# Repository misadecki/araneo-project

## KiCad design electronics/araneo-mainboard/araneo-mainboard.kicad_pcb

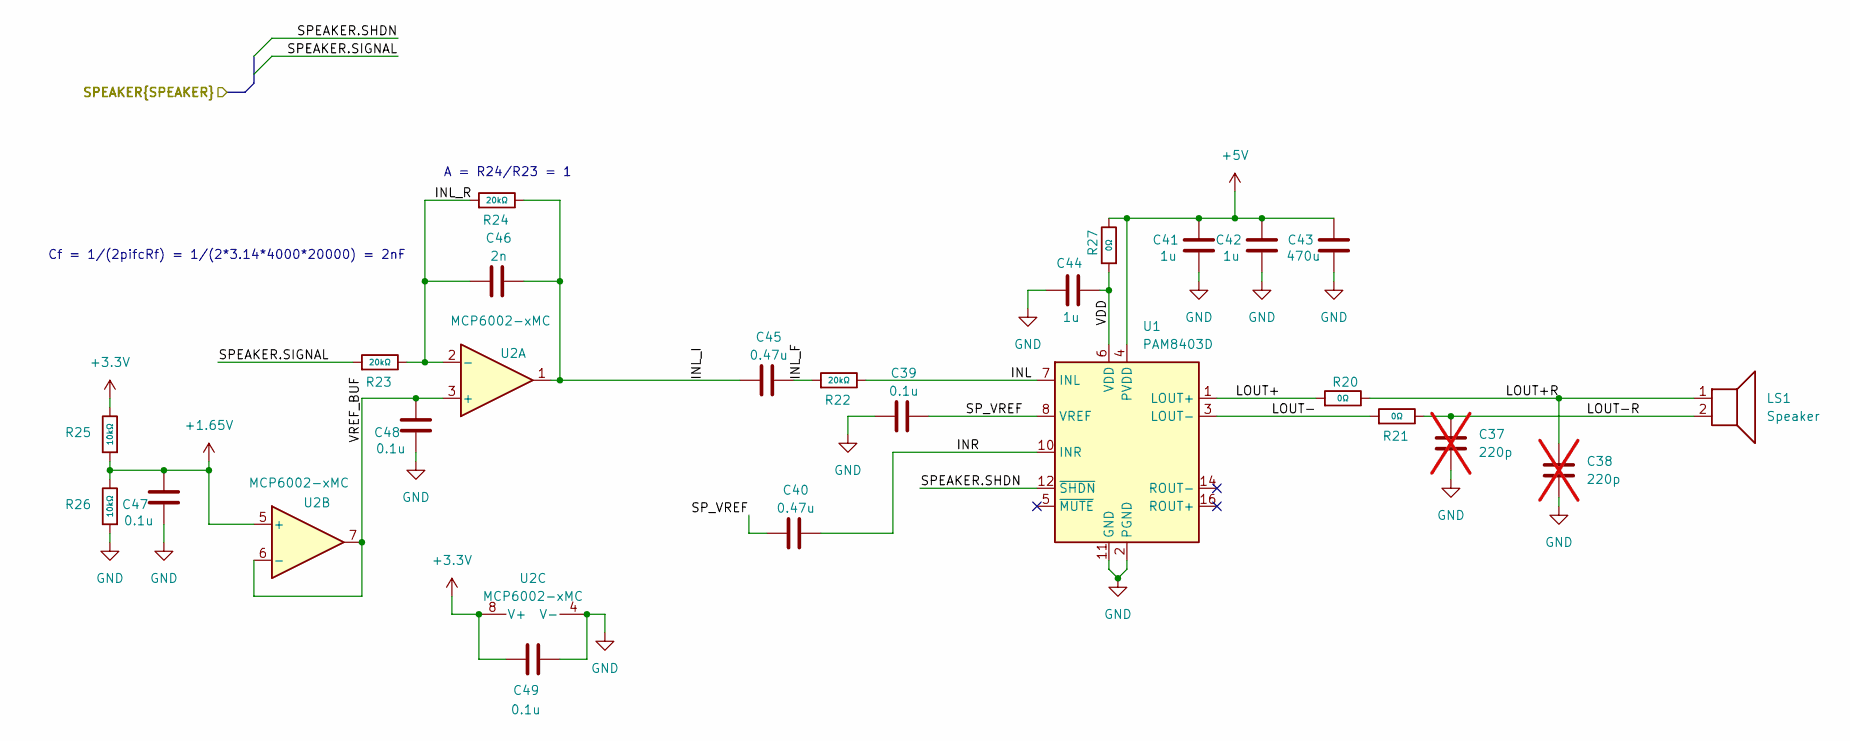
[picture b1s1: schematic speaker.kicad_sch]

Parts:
C37, C38: 220p; C_0603; not fitted
C39, C47, C48, C49: 0.1u; C_0402
C40, C45: 0.47u; C_0402
C41, C42, C44: 1u; C_0402
C43: 470u; CP_Radial_D10.0mm_P5.00mm
C46: 2n; C_0603
LS1: Speaker; ScrewTerminal_1x02_P3.5mm_Blue
R20, R21, R27: 0Ω; R_0603; Overload Voltage (Max) 50V; Tolerance ±1%; Part 0402WGF1201TCE; LCSC C25862
R22, R23, R24: 20kΩ; R_0603; Overload Voltage (Max) 50V; Tolerance ±1%; Part 0402WGF1201TCE; LCSC C25862
R25, R26: 10kΩ; R_0402; Overload Voltage (Max) 50V; Tolerance ±1%; Part 0402WGF1201TCE; LCSC C25862
U1: PAM8403D; SOIC-16_3.9x9.9mm_P1.27mm
U2: MCP6002-xMC; SOIC-8_L4.9-W3.9-P1.27-LS6.0-BL

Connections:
+1.65V: C47.2, R25.1, R26.2, U2.5 (+)
+3.3V: C49.2, R25.2, U2.8 (V+); also elsewhere on the board
+5V: C41.2, C42.2, C43.2, R27.2, U1.4 (PVDD), U1.13 (PVDD); also elsewhere on the board
/MCU/SPEAKER.SHDN: U1.12 (~SHDN); also elsewhere on the board
/MCU/SPEAKER.SIGNAL: R23.1; also elsewhere on the board
/Speaker/INL: R22.2, U1.7 (INL)
/Speaker/INL_F: C45.2, R22.1
/Speaker/INL_I: C45.1, C46.2, R24.2, U2.1
/Speaker/INL_R: C46.1, R23.2, R24.1, U2.2 (-)
/Speaker/INR: C40.2, U1.10 (INR)
/Speaker/LOUT+: R20.1, U1.1 (LOUT+)
/Speaker/LOUT+R: C38.1, LS1.1, R20.2
/Speaker/LOUT-: R21.1, U1.3 (LOUT-)
/Speaker/LOUT-R: C37.1, LS1.2, R21.2
/Speaker/SP_VREF: C39.2, C40.1, U1.8 (VREF)
/Speaker/VDD: C44.1, R27.1, U1.6 (VDD)
/Speaker/VREF_BUF: C48.2, U2.3 (+), U2.6 (-), U2.7
GND: C37.2, C38.2, C39.1, C41.1, C42.1, C43.1, C44.2, C47.1, C48.1, C49.1, R26.1, U1.2 (PGND), U1.11 (GND), U1.15 (PGND), U2.4 (V-); also elsewhere on the board

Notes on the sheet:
Cf = 1/(2pifcRf) = 1/(2*3.14*4000*20000) = 2nF
A = R24/R23 = 1

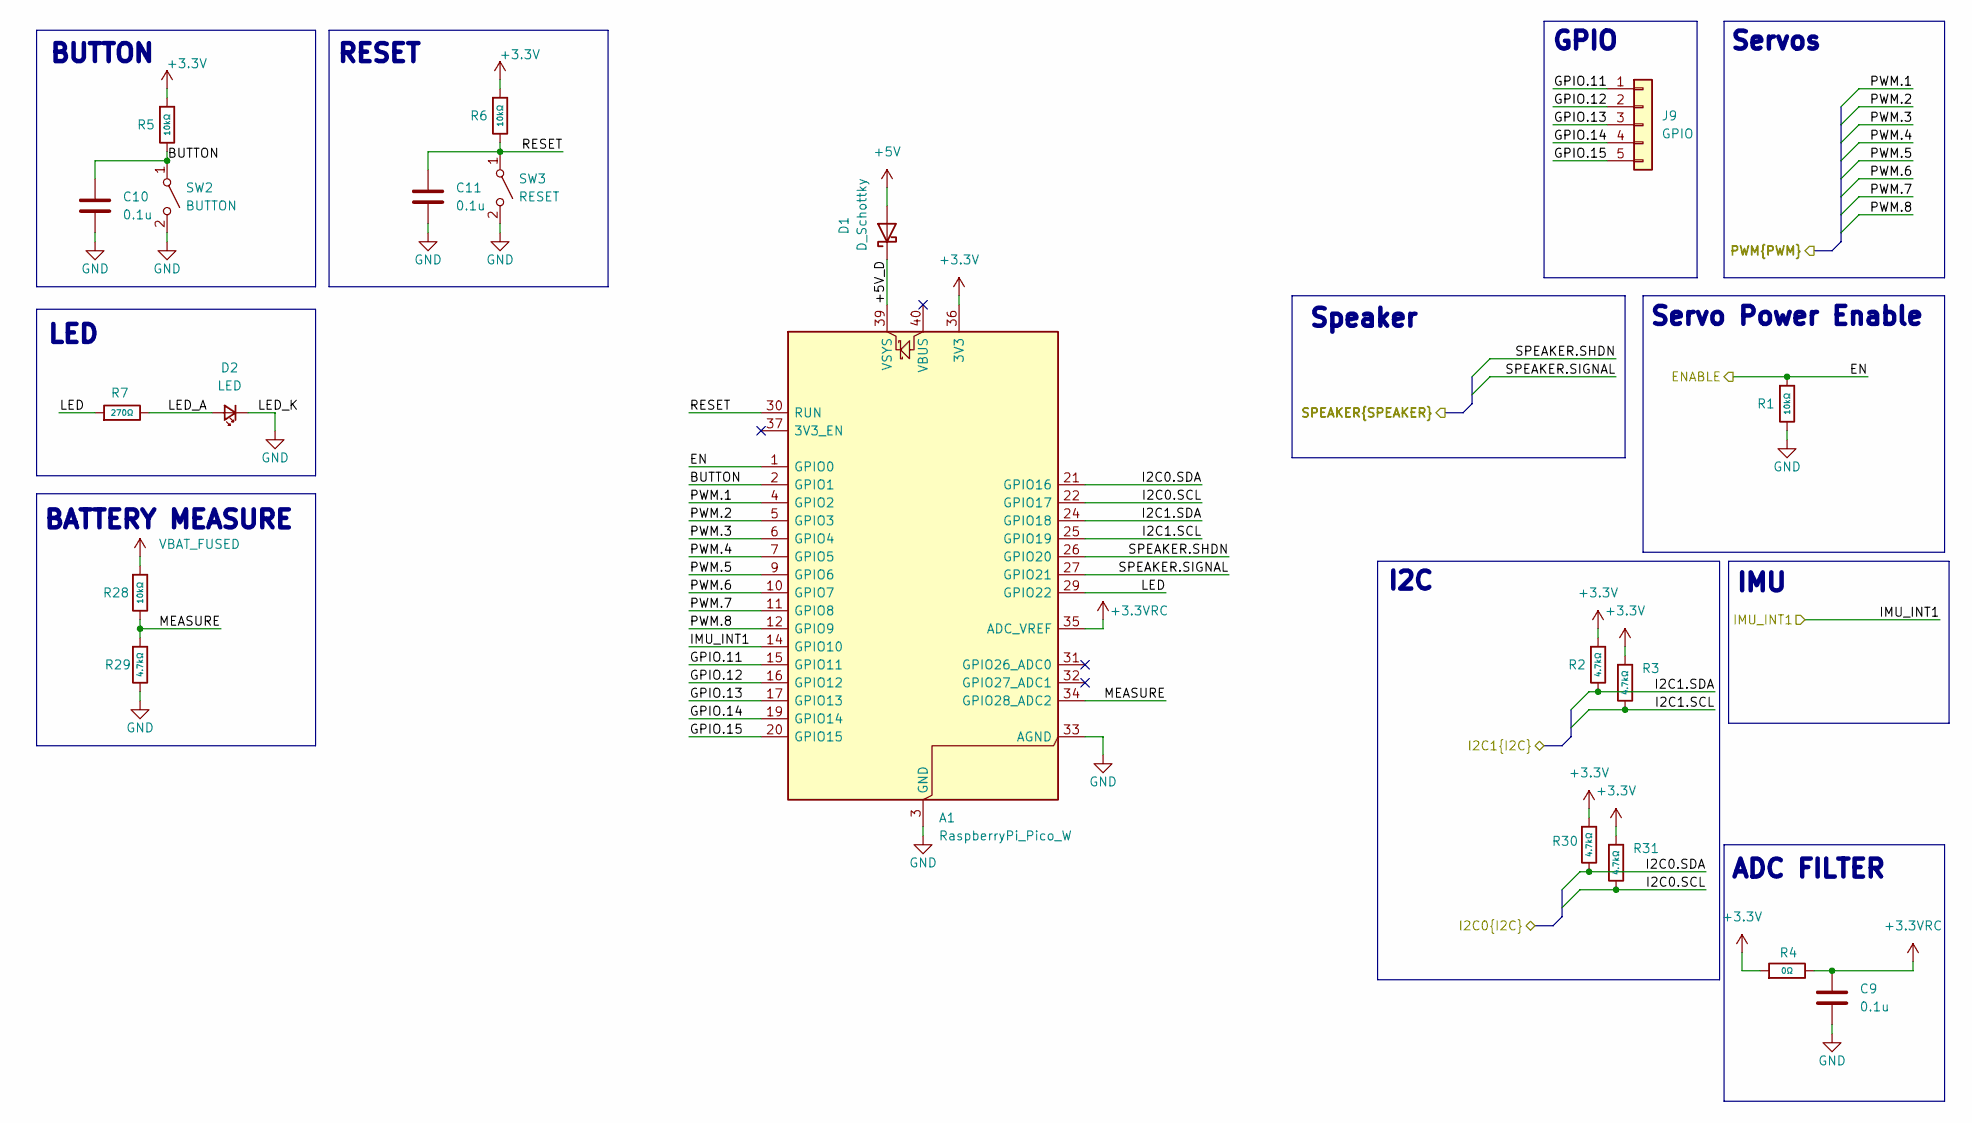
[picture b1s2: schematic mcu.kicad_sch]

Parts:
A1: RaspberryPi_Pico_W; RaspberryPi_Pico_Common_THT
C9: 0.1u; C_0603
C10, C11: 0.1u; C_0402
D1: D_Schottky; SOD-123
D2: LED; D_0603
J9: GPIO; PinHeader_1x05_P2.54mm_Vertical
R1, R5, R6, R28: 10kΩ; R_0402; Overload Voltage (Max) 50V; Tolerance ±1%; Part 0402WGF1201TCE; LCSC C25862
R2, R3, R29, R30, R31: 4.7kΩ; R_0402; Overload Voltage (Max) 50V; Tolerance ±1%; Part 0402WGF1201TCE; LCSC C25862
R4: 0Ω; R_0603; Overload Voltage (Max) 50V; Tolerance ±1%; Part 0402WGF1201TCE; LCSC C25862
R7: 270Ω; R_0603; Overload Voltage (Max) 50V; Tolerance ±1%; Part 0402WGF1201TCE; LCSC C25862
SW2: BUTTON; ScrewTerminal_1x02_P3.5mm_Blue
SW3: RESET; SW_SPST_TL3305B

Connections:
+3.3V: A1.36 (3V3), R2.1, R3.1, R4.1, R5.1, R6.1, R30.1, R31.1; also elsewhere on the board
+3.3VRC: A1.35 (ADC_VREF), C9.1, R4.2
+5V: D1.2 (A); also elsewhere on the board
/IMU/I2C1.SCL: A1.25 (GPIO19), R3.2; also elsewhere on the board
/IMU/I2C1.SDA: A1.24 (GPIO18), R2.2; also elsewhere on the board
/MCU/+5V_D: A1.39 (VSYS), D1.1 (K)
/MCU/BUTTON: A1.2 (GPIO1), C10.1, R5.2, SW2.1 (A)
/MCU/EN: A1.1 (GPIO0), R1.1; also elsewhere on the board
/MCU/GPIO.11: A1.15 (GPIO11), J9.1
/MCU/GPIO.12: A1.16 (GPIO12), J9.2
/MCU/GPIO.13: A1.17 (GPIO13), J9.3
/MCU/GPIO.14: A1.19 (GPIO14), J9.4
/MCU/GPIO.15: A1.20 (GPIO15), J9.5
/MCU/I2C0.SCL: A1.22 (GPIO17), R31.2; also elsewhere on the board
/MCU/I2C0.SDA: A1.21 (GPIO16), R30.2; also elsewhere on the board
/MCU/IMU_INT1: A1.14 (GPIO10); also elsewhere on the board
/MCU/LED: A1.29 (GPIO22), R7.1
/MCU/LED_A: D2.2 (A), R7.2
/MCU/MEASURE: A1.34 (GPIO28_ADC2), R28.2, R29.1
/MCU/PWM.1: A1.4 (GPIO2); also elsewhere on the board
/MCU/PWM.2: A1.5 (GPIO3); also elsewhere on the board
/MCU/PWM.3: A1.6 (GPIO4); also elsewhere on the board
/MCU/PWM.4: A1.7 (GPIO5); also elsewhere on the board
/MCU/PWM.5: A1.9 (GPIO6); also elsewhere on the board
/MCU/PWM.6: A1.10 (GPIO7); also elsewhere on the board
/MCU/PWM.7: A1.11 (GPIO8); also elsewhere on the board
/MCU/PWM.8: A1.12 (GPIO9); also elsewhere on the board
/MCU/RESET: A1.30 (RUN), C11.1, R6.2, SW3.1 (A)
/MCU/SPEAKER.SHDN: A1.26 (GPIO20); also elsewhere on the board
/MCU/SPEAKER.SIGNAL: A1.27 (GPIO21); also elsewhere on the board
GND: A1.3 (GND), A1.8 (GND), A1.13 (GND), A1.18 (GND), A1.23 (GND), A1.28 (GND), A1.33 (AGND), A1.38 (GND), C9.2, C10.2, C11.2, D2.1 (K), R1.2, R29.2, SW2.2 (B), SW3.2 (B); also elsewhere on the board
VBAT_FUSED: R28.1; also elsewhere on the board

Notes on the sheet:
I2C
RESET
BATTERY MEASURE
IMU
GPIO
LED
Servo Power Enable
Servos
BUTTON
Speaker
ADC FILTER

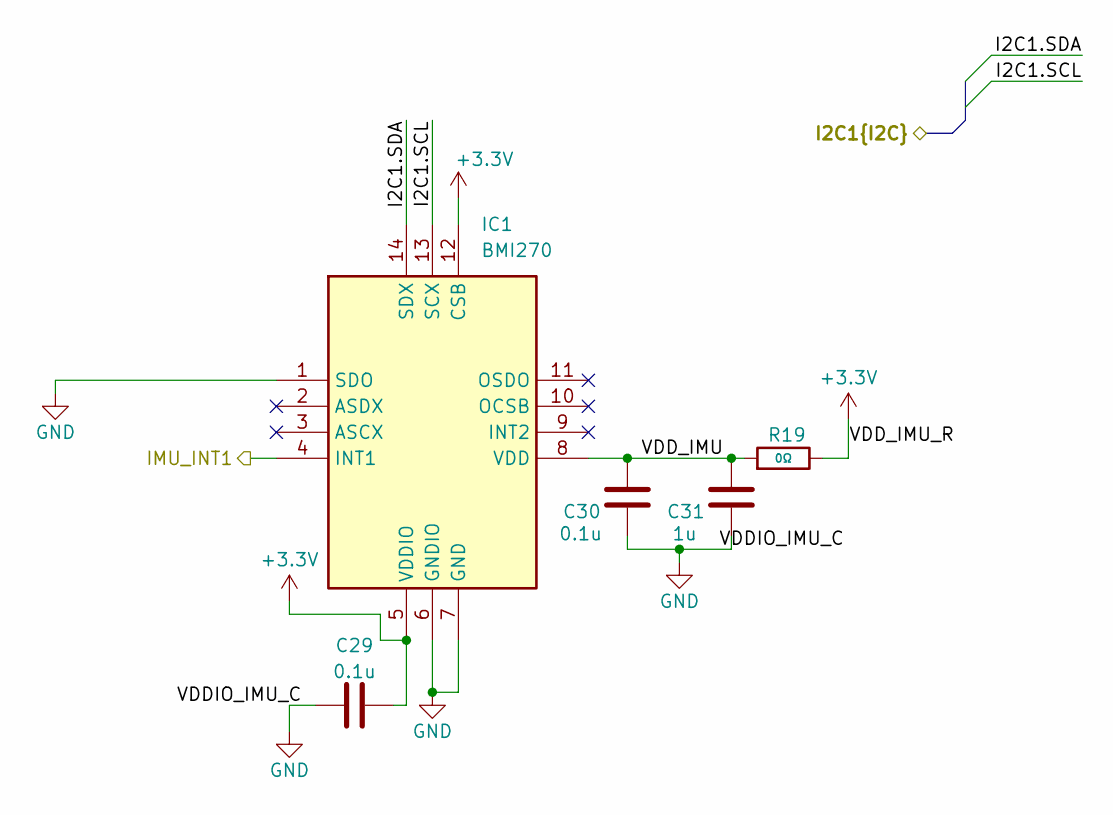
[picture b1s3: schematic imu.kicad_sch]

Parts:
C29, C30: 0.1u; C_0402
C31: 1u; C_0402
IC1: BMI270; Mouser Part Number 262-BMI270
R19: 0Ω; R_0603; Overload Voltage (Max) 50V; Tolerance ±1%; Part 0402WGF1201TCE; LCSC C25862

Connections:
+3.3V: C29.2, IC1.5 (VDDIO), IC1.12 (CSB), R19.2; also elsewhere on the board
/IMU/I2C1.SCL: IC1.13 (SCX); also elsewhere on the board
/IMU/I2C1.SDA: IC1.14 (SDX); also elsewhere on the board
/IMU/VDD_IMU: C30.2, C31.2, IC1.8 (VDD), R19.1
/MCU/IMU_INT1: IC1.4 (INT1); also elsewhere on the board
GND: C29.1, C30.1, C31.1, IC1.1 (SDO), IC1.6 (GNDIO), IC1.7 (GND); also elsewhere on the board

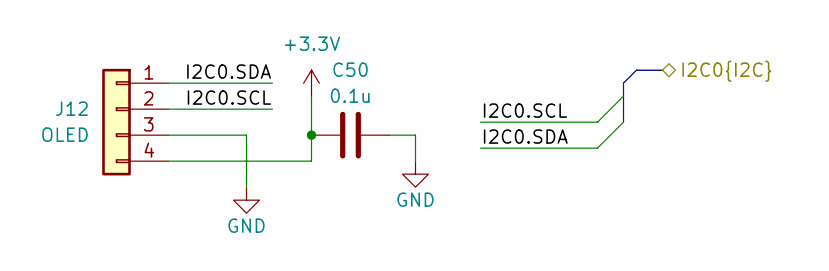
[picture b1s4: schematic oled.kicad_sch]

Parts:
C50: 0.1u; C_0402
J12: OLED; JST_XH_B4B-XH-A_1x04_P2.50mm_Vertical

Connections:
+3.3V: C50.1, J12.4; also elsewhere on the board
/MCU/I2C0.SCL: J12.2; also elsewhere on the board
/MCU/I2C0.SDA: J12.1; also elsewhere on the board
GND: C50.2, J12.3; also elsewhere on the board

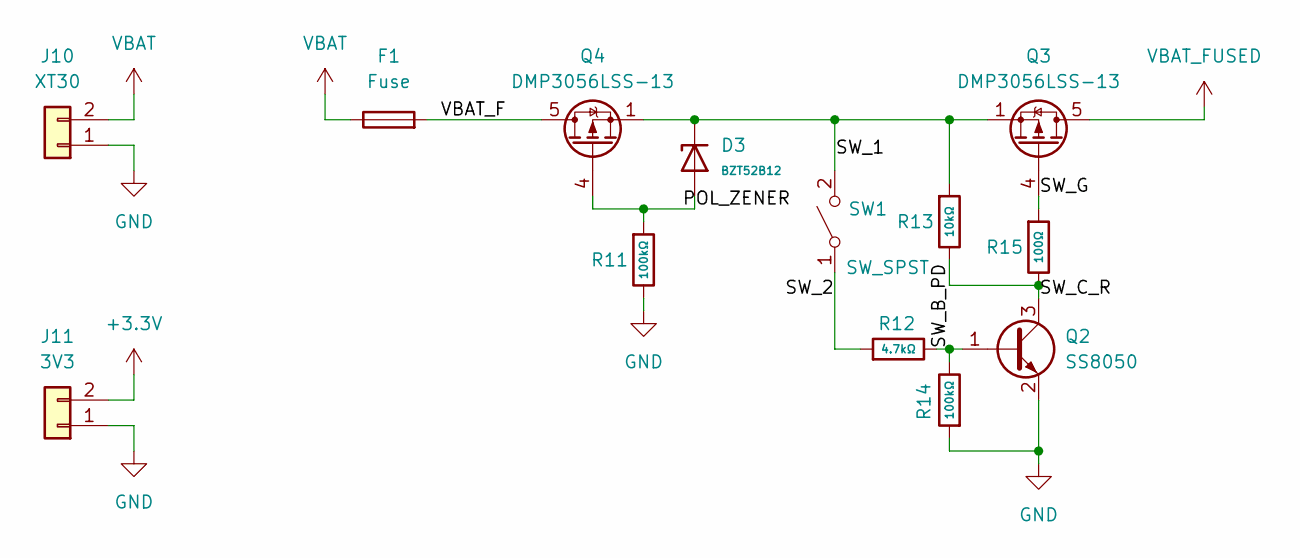
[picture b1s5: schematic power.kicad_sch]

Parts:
D3: BZT52B12; D_SOD-123; Zener Voltage (Range) 11.76V~12.24V; Zener Voltage (Nom) 12V; Part BZT52B12; LCSC C22395569
F1: Fuse; 3568
J10: XT30; AMASS_XT30U-F_1x02_P5.0mm_Vertical
J11: 3V3; PinHeader_1x02_P2.54mm_Vertical
Q2: SS8050; SOT-23
Q3, Q4: DMP3056LSS-13; SO-8
R11, R14: 100kΩ; R_0402; Overload Voltage (Max) 50V; Tolerance ±1%; Part 0402WGF1201TCE; LCSC C25862
R12: 4.7kΩ; R_0402; Overload Voltage (Max) 50V; Tolerance ±1%; Part 0402WGF1201TCE; LCSC C25862
R13: 10kΩ; R_0402; Overload Voltage (Max) 50V; Tolerance ±1%; Part 0402WGF1201TCE; LCSC C25862
R15: 100Ω; R_0402; Overload Voltage (Max) 50V; Tolerance ±1%; Part 0402WGF1201TCE; LCSC C25862
SW1: SW_SPST; ScrewTerminal_1x02_P3.5mm_Blue

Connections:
+3.3V: J11.2; also elsewhere on the board
/Power/POL_ZENER: D3.2, Q4.4 (G), R11.1
/Power/SW_1: D3.1, Q3.1 (S), Q3.2 (S), Q3.3 (S), Q4.1 (S), Q4.2 (S), Q4.3 (S), R13.1, SW1.2 (B)
/Power/SW_2: R12.1, SW1.1 (A)
/Power/SW_B_PD: Q2.1 (B), R12.2, R14.2
/Power/SW_C_R: Q2.3 (C), R13.2, R15.2
/Power/SW_G: Q3.4 (G), R15.1
/Power/VBAT_F: F1.2, Q4.5 (D), Q4.6 (D), Q4.7 (D), Q4.8 (D)
GND: J10.1, J11.1, Q2.2 (E), R11.2, R14.1; also elsewhere on the board
VBAT: F1.1, J10.2
VBAT_FUSED: Q3.5 (D), Q3.6 (D), Q3.7 (D), Q3.8 (D); also elsewhere on the board

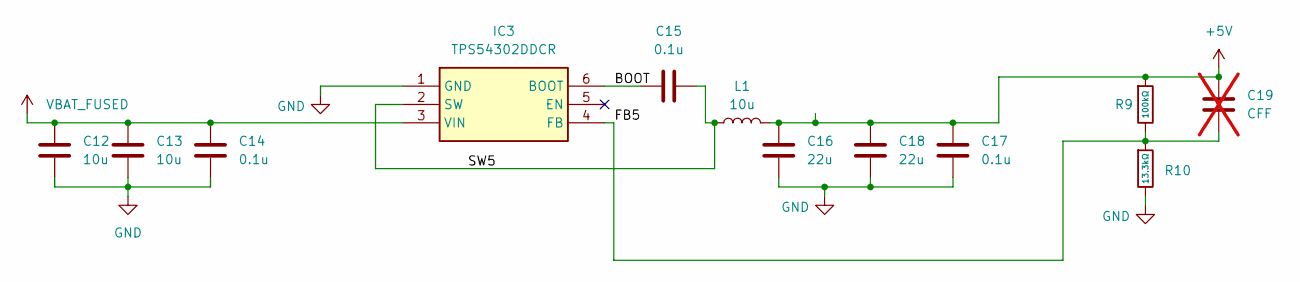
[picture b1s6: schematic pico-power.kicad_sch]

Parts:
C12, C13: 10u; C_0603
C14, C15, C17: 0.1u; C_0402
C16, C18: 22u; C_0805
C19: CFF; C_0603; not fitted
IC3: TPS54302DDCR; SOT95P280X110-6N; Mouser Part Number 595-TPS54302DDCR
L1: 10u; PA4302103NLT
R9: 100kΩ; R_0402; Overload Voltage (Max) 50V; Tolerance ±1%; Part 0402WGF1201TCE; LCSC C25862
R10: 13.3kΩ; R_0402; Overload Voltage (Max) 50V; Tolerance ±1%; Part 0402WGF1201TCE; LCSC C25862

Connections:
+5V: C16.1, C17.2, C18.1, C19.2, L1.2, R9.1; also elsewhere on the board
/Power 5V/BOOT: C15.1, IC3.6 (BOOT)
/Power 5V/FB5: C19.1, IC3.4 (FB), R9.2, R10.1
/Power 5V/SW5: C15.2, IC3.2 (SW), L1.1
GND: C12.2, C13.2, C14.2, C16.2, C17.1, C18.2, IC3.1 (GND), R10.2; also elsewhere on the board
VBAT_FUSED: C12.1, C13.1, C14.1, IC3.3 (VIN); also elsewhere on the board

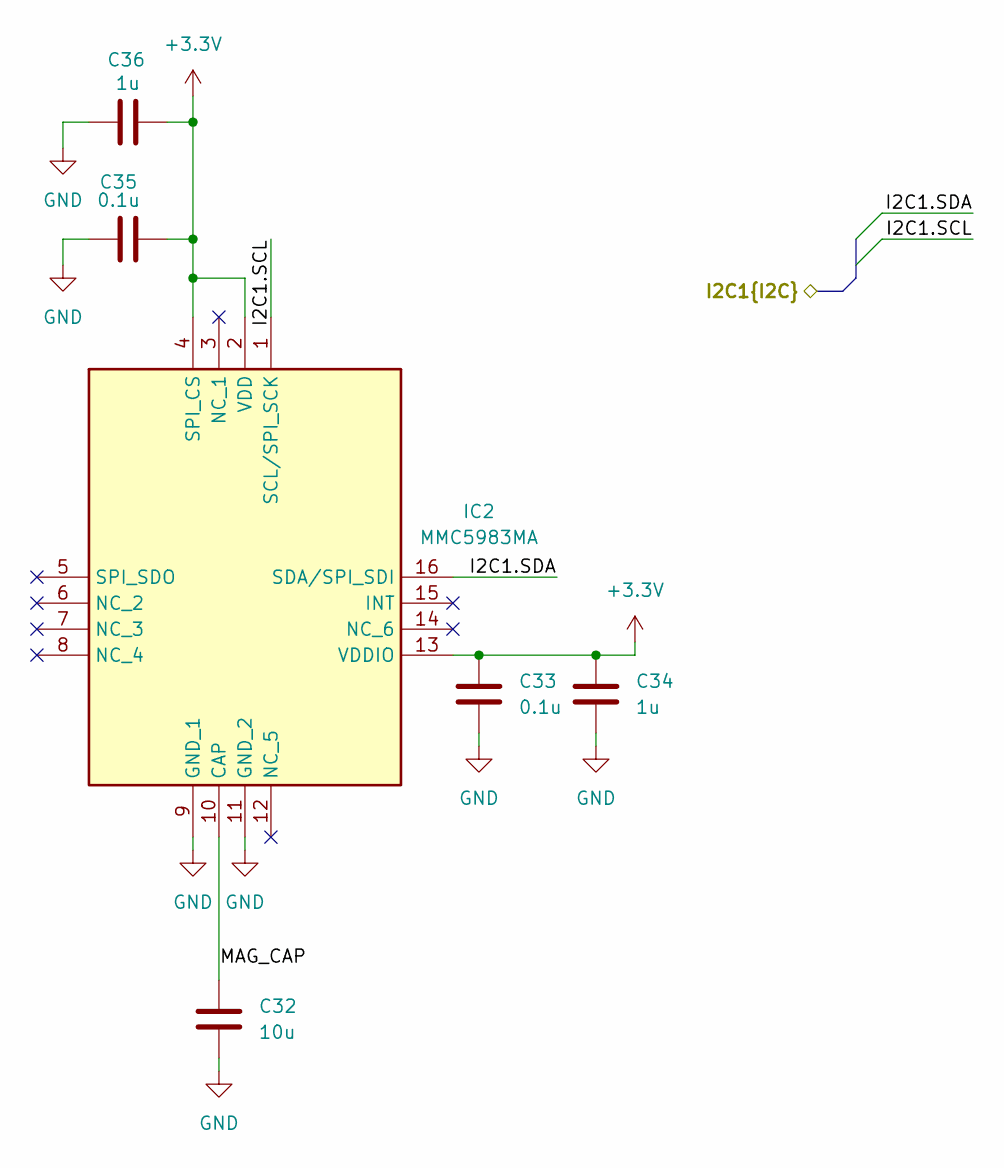
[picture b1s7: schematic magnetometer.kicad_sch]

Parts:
C32: 10u; C_0603
C33, C35: 0.1u; C_0402
C34, C36: 1u; C_0402
IC2: MMC5983MA; Mouser Part Number 438-MMC5983MA

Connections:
+3.3V: C33.1, C34.1, C35.2, C36.2, IC2.2 (VDD), IC2.4 (SPI_CS), IC2.13 (VDDIO); also elsewhere on the board
/IMU/I2C1.SCL: IC2.1 (SCL/SPI_SCK); also elsewhere on the board
/IMU/I2C1.SDA: IC2.16 (SDA/SPI_SDI); also elsewhere on the board
/Magnetometer/MAG_CAP: C32.1, IC2.10 (CAP)
GND: C32.2, C33.2, C34.2, C35.1, C36.1, IC2.9 (GND_1), IC2.11 (GND_2); also elsewhere on the board

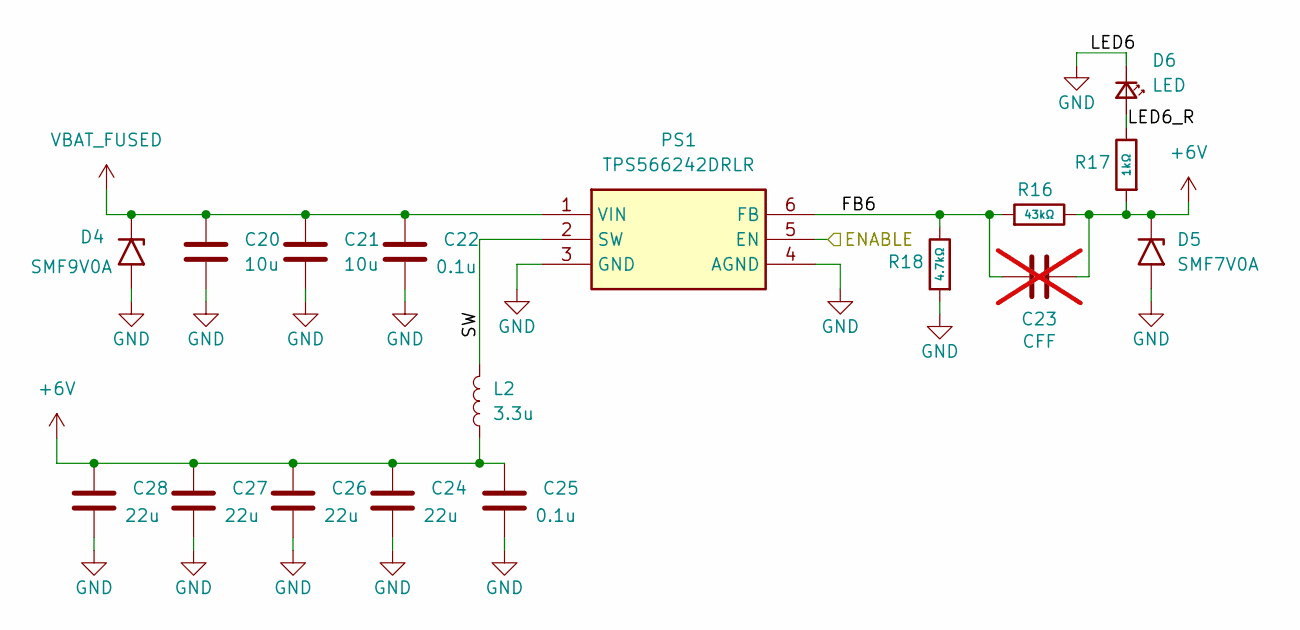
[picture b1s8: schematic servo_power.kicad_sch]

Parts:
C20, C21: 10u; C_0603
C22, C25: 0.1u; C_0402
C23: CFF; C_0603; not fitted
C24, C26, C27, C28: 22u; C_0805
D4: SMF9V0A; D_SMF
D5: SMF7V0A; D_SOD-123
D6: LED; D_0603
L2: 3.3u; INDPM112100X400N
PS1: TPS566242DRLR; SOT50P160X60-6N; Mouser Part Number 595-TPS566242DRLR
R16: 43kΩ; R_0402; Overload Voltage (Max) 50V; Tolerance ±1%; Part 0402WGF1201TCE; LCSC C25862
R17: 1kΩ; R_0402; Overload Voltage (Max) 50V; Tolerance ±1%; Part 0402WGF1201TCE; LCSC C25862
R18: 4.7kΩ; R_0402; Overload Voltage (Max) 50V; Tolerance ±1%; Part 0402WGF1201TCE; LCSC C25862

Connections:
+6V: C23.2, C24.1, C25.1, C26.1, C27.1, C28.1, D5.1 (A1), L2.1, R16.2, R17.1; also elsewhere on the board
/MCU/EN: PS1.5 (EN); also elsewhere on the board
/Power 6V/FB6: C23.1, PS1.6 (FB), R16.1, R18.2
/Power 6V/LED6_R: D6.2 (A), R17.2
/Power 6V/SW: L2.2, PS1.2 (SW)
GND: C20.2, C21.2, C22.2, C24.2, C25.2, C26.2, C27.2, C28.2, D4.2 (A2), D5.2 (A2), D6.1 (K), PS1.3 (GND), PS1.4 (AGND), R18.1; also elsewhere on the board
VBAT_FUSED: C20.1, C21.1, C22.1, D4.1 (A1), PS1.1 (VIN); also elsewhere on the board

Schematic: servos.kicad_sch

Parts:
C1, C2, C3, C4, C5, C6, C7, C8: 0.1u; C_0402
J1: Servo1; PinHeader_1x03_P2.54mm_Vertical
J2: Servo2; PinHeader_1x03_P2.54mm_Vertical
J3: Servo3; PinHeader_1x03_P2.54mm_Vertical
J4: Servo4; PinHeader_1x03_P2.54mm_Vertical
J5: Servo5; PinHeader_1x03_P2.54mm_Vertical
J6: Servo7; PinHeader_1x03_P2.54mm_Vertical
J7: Servo6; PinHeader_1x03_P2.54mm_Vertical
J8: Servo8; PinHeader_1x03_P2.54mm_Vertical

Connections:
+6V: C1.1, C2.1, C3.1, C4.1, C5.1, C6.1, C7.1, C8.1, J1.2, J2.2, J3.2, J4.2, J5.2, J6.2, J7.2, J8.2; also elsewhere on the board
/MCU/PWM.1: J1.1; also elsewhere on the board
/MCU/PWM.2: J2.1; also elsewhere on the board
/MCU/PWM.3: J3.1; also elsewhere on the board
/MCU/PWM.4: J4.1; also elsewhere on the board
/MCU/PWM.5: J5.1; also elsewhere on the board
/MCU/PWM.6: J7.1; also elsewhere on the board
/MCU/PWM.7: J6.1; also elsewhere on the board
/MCU/PWM.8: J8.1; also elsewhere on the board
GND: C1.2, C2.2, C3.2, C4.2, C5.2, C6.2, C7.2, C8.2, J1.3, J2.3, J3.3, J4.3, J5.3, J6.3, J7.3, J8.3; also elsewhere on the board

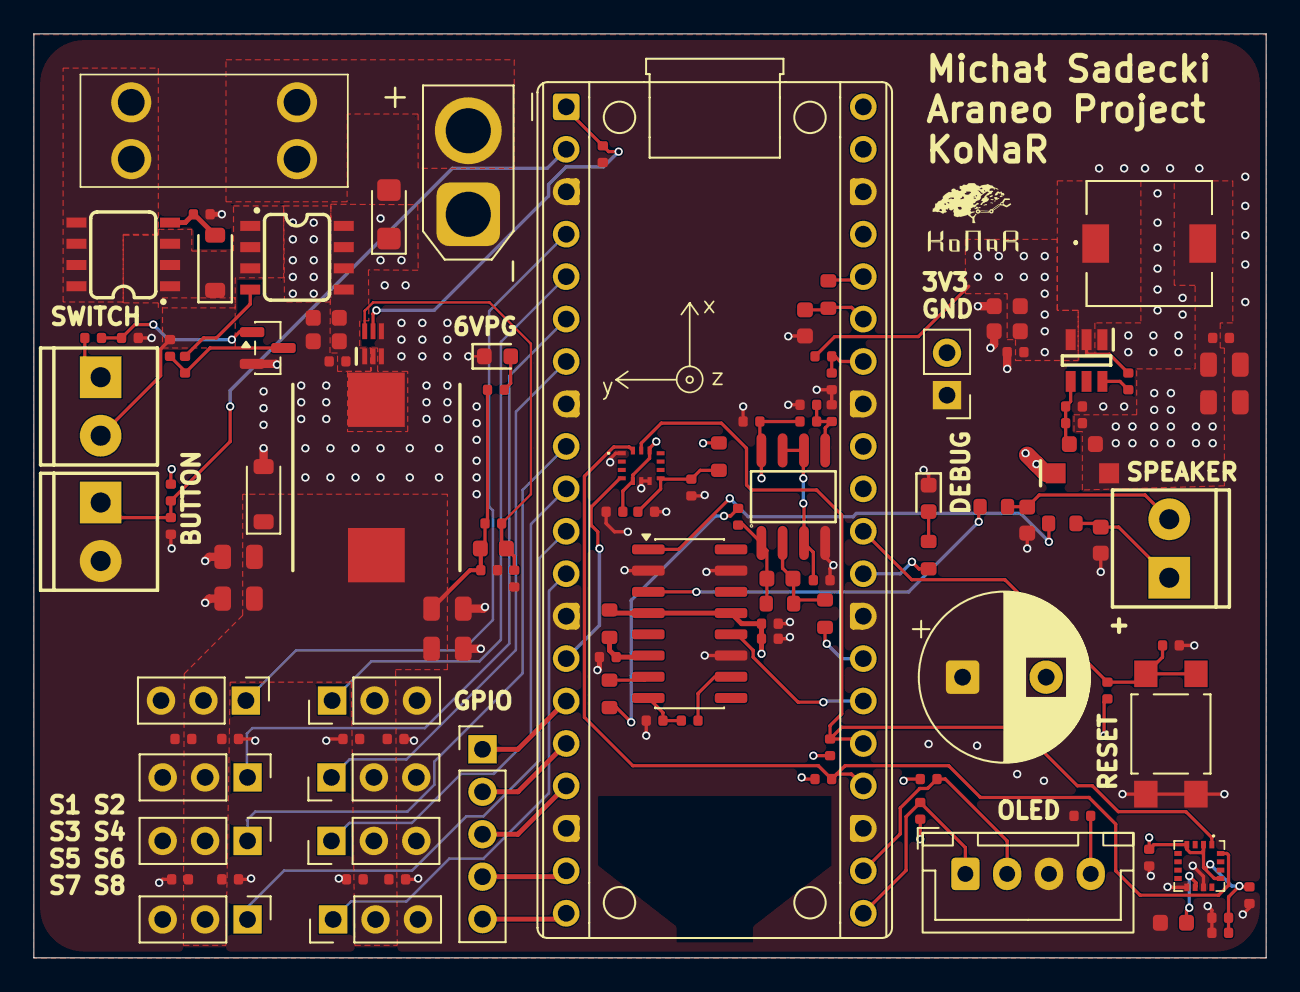
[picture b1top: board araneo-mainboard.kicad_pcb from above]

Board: 4 copper layers, 73.8 x 55.3 mm, 116 parts (0 on the bottom side), 62 nets.

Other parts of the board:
konar1: LOGO; konar
